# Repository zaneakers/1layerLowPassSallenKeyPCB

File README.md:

# 1layerLowPassSallenKeyPCB
1layerLowPassSallenKeyPCB

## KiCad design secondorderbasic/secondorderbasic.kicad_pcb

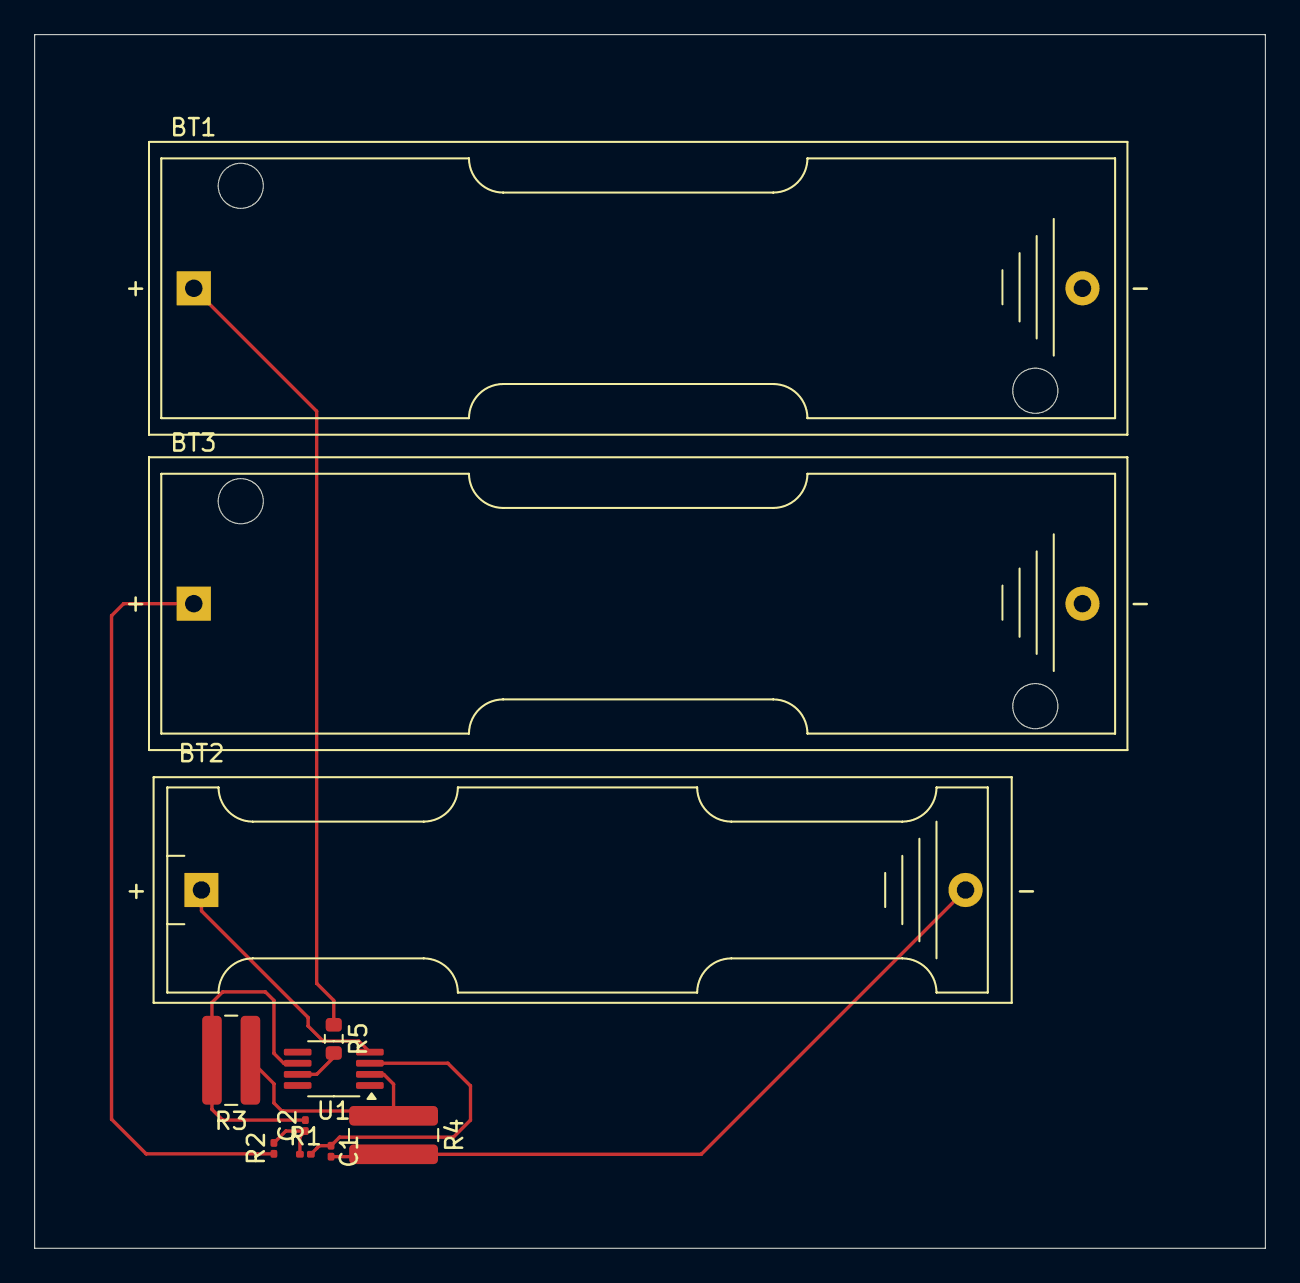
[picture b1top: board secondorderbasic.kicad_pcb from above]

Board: 2 copper layers, 72.0 x 71.0 mm, 11 parts (0 on the bottom side), 9 nets.

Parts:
BT1, BT3: 5V; BatteryHolder_Keystone_2460_1xAA
BT2: 2.5V; BatteryHolder_Keystone_2466_1xAAA
C1, C2: 2uF; C_0201_0603Metric
R1, R2: 1000; R_0201_0603Metric
R3, R4: 10000; R_1020_2550Metric
R5: 0; R_0603_1608Metric
U1: OP1177ARM; MSOP-8_3x3mm_P0.65mm

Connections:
/negativefeedback: C2.2, R3.2, U1.6
/positivefeedback: C2.1, R1.1, R2.2
GND: BT1.2 (-), BT2.2 (-), BT3.2 (-), C1.2, R4.2
unnamed: BT1.1 (+), R5.1
unnamed: BT2.1 (+), U1.4 (V-)
unnamed: BT3.1 (+), R2.1
unnamed: C1.1, R1.2, U1.3 (+)
unnamed: R3.1, R4.1, U1.2 (-)
unnamed: R5.2, U1.7 (V+)

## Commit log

2025-05-28 test1pls work
2025-05-28 test
2025-05-28 testagain
